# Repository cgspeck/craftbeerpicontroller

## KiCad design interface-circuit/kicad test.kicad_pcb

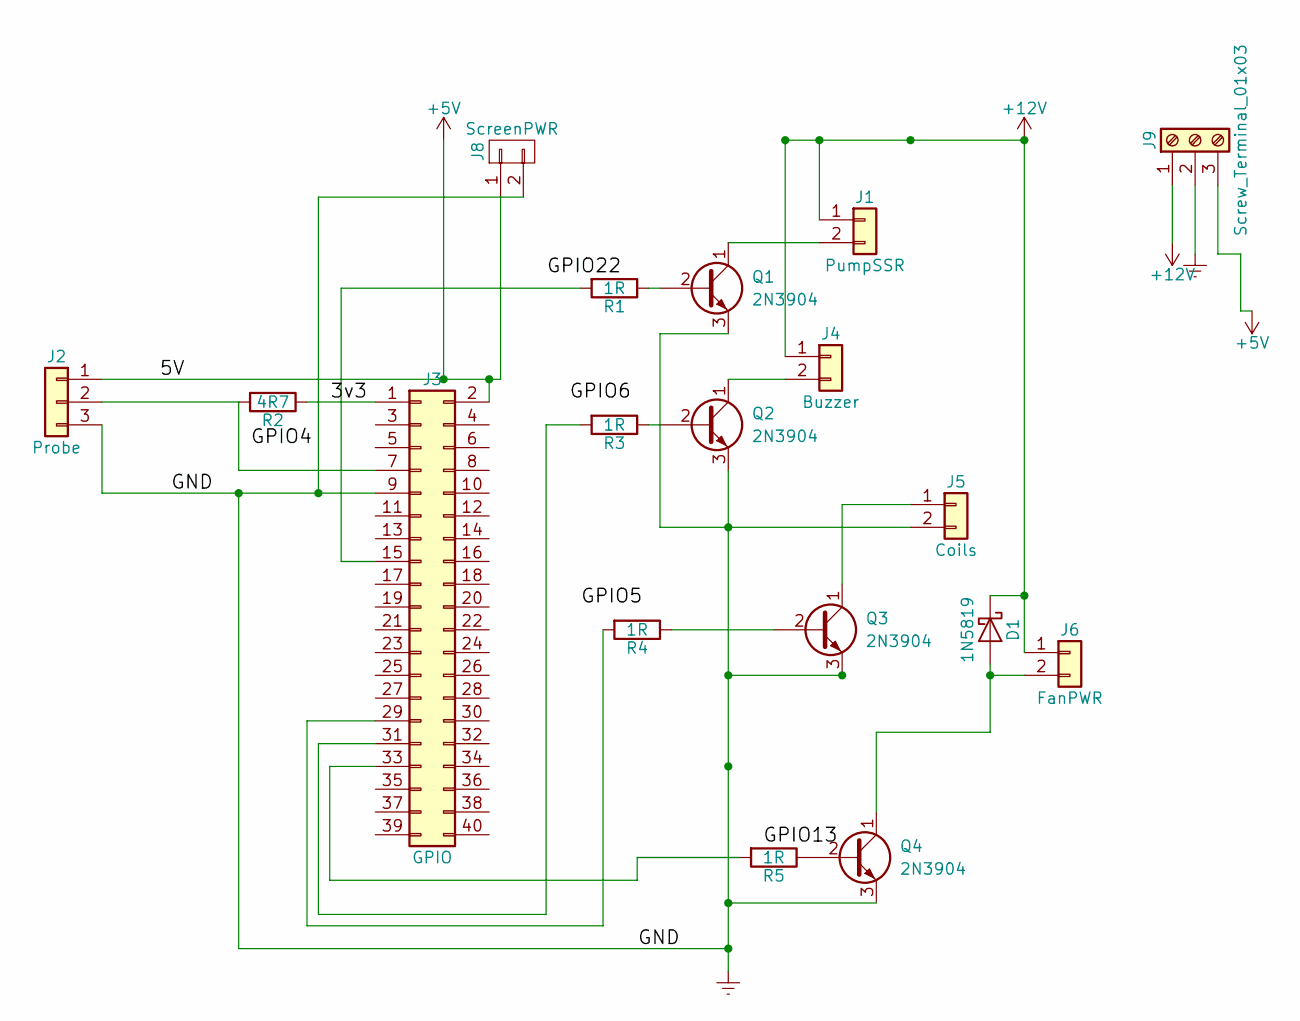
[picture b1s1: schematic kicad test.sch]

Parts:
D1: 1N5819; D_DO-41_SOD81_P10.16mm_Horizontal
J1: PumpSSR; TerminalBlock_bornier-2_P5.08mm
J2: Probe; TerminalBlock_bornier-3_P5.08mm
J3: GPIO; Pin_Header_Straight_2x20_Pitch2.54mm
J4: Buzzer; TerminalBlock_bornier-2_P5.08mm
J5: Coils; TerminalBlock_bornier-2_P5.08mm
J6: FanPWR; TerminalBlock_bornier-2_P5.08mm
J8: ScreenPWR; TerminalBlock_bornier-2_P5.08mm
J9: Screw_Terminal_01x03; TerminalBlock_bornier-3_P5.08mm
Q1, Q2, Q3, Q4: 2N3904; TO-92_Inline_Narrow_Oval
R1, R3, R4, R5: 1R; R_Axial_DIN0309_L9.0mm_D3.2mm_P15.24mm_Horizontal
R2: 4R7; R_Axial_DIN0309_L9.0mm_D3.2mm_P15.24mm_Horizontal

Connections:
+5V: J2.1, J3.2, J8.1, J9.3
+12V: D1.1 (K), J1.1, J4.1, J6.1, J9.1
/3v3: J3.1, R2.1
Earth: J2.3, J3.9, J5.2, J8.2, J9.2, Q1.3 (E), Q2.3 (E), Q3.3 (E), Q4.3 (E)
unnamed: D1.2 (A), J6.2, Q4.1 (C)
unnamed: J1.2, Q1.1 (C)
unnamed: J2.2, J3.7, R2.2
unnamed: J3.15, R1.2
unnamed: J3.29, R4.2
unnamed: J3.31, R3.2
unnamed: J3.33, R5.2
unnamed: J4.2, Q2.1 (C)
unnamed: J5.1, Q3.1 (C)
unnamed: Q1.2 (B), R1.1
unnamed: Q2.2 (B), R3.1
unnamed: Q3.2 (B), R4.1
unnamed: Q4.2 (B), R5.1

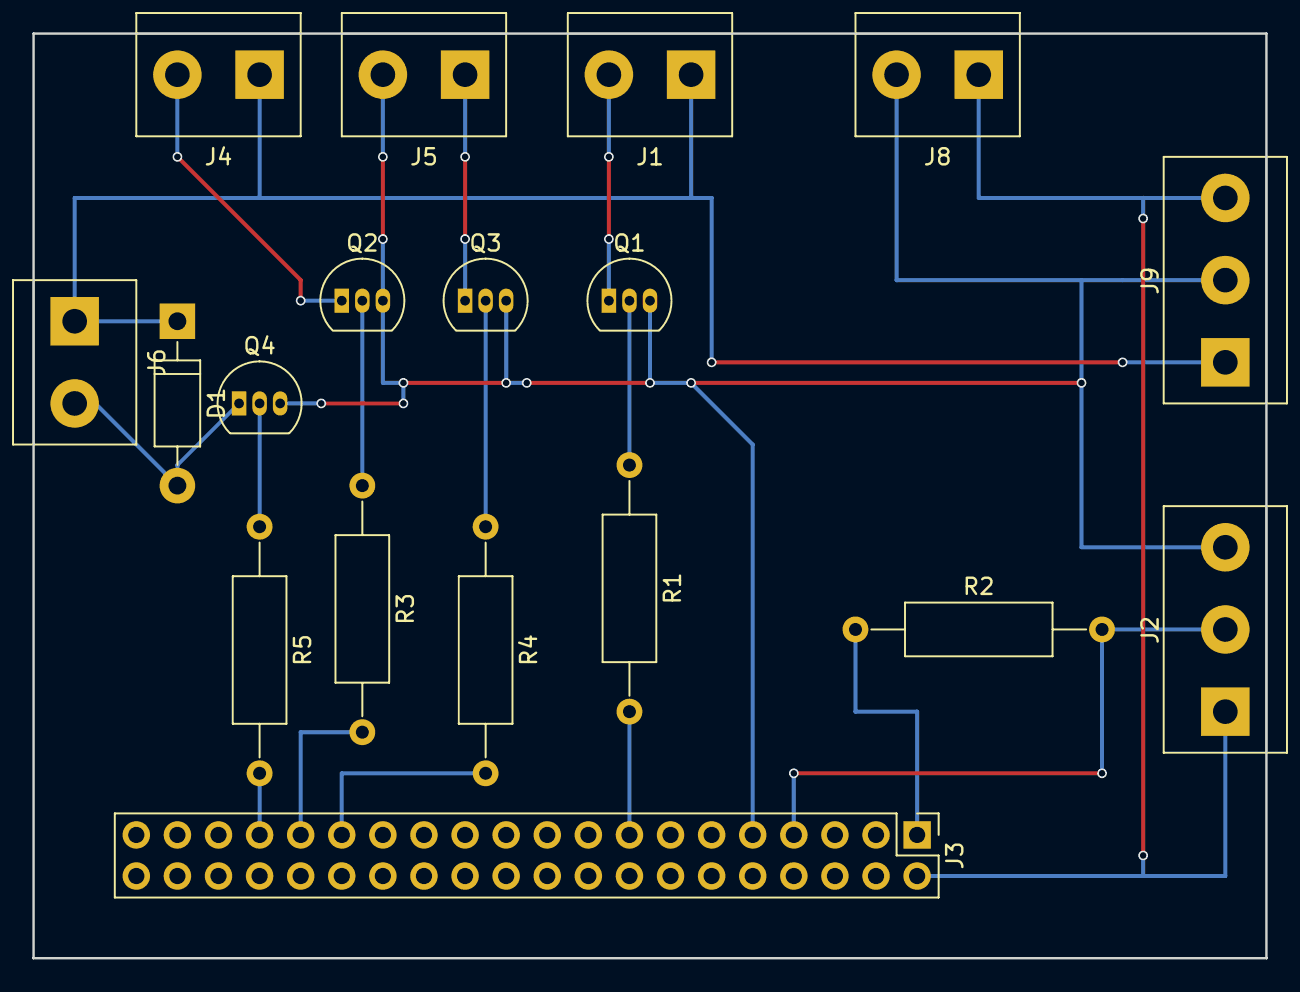
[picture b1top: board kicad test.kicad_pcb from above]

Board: 2 copper layers, 76.2 x 57.2 mm, 18 parts (0 on the bottom side), 17 nets.

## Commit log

2018-03-04 Adding the Openscad designs for the controller
2018-03-04 Adding datasheets and kicad circuit
2018-03-04 Debugging board revealed that the transistors on the PCB plan have reversed pin assignments. This commit fixes it.
2018-03-05 A frame for the screen aperture
2018-03-05 I corrected the issue with the J4 connector
2018-03-05 I found that the Pi could not sink enough power from the USB connection for both itself and the official screen, so I moved the screen's power connecter such that it is now driven directly by the PSU
2018-03-06 Final adjustment prior to first print
2018-03-13 Needed to replace the push fit controller inlets with smaller flange mounted inlets, this cover makes up the gap
2018-03-13 Cut outs for front pilot lights with provisional value of base width
2018-03-14 Print out light spacing
2018-07-13 Add transistor control of fan, make pins match 3rd party board, switch to screw terminals
2018-07-15 New PCB layout using only screw terminals
2019-04-25 GPIO pin test read script
